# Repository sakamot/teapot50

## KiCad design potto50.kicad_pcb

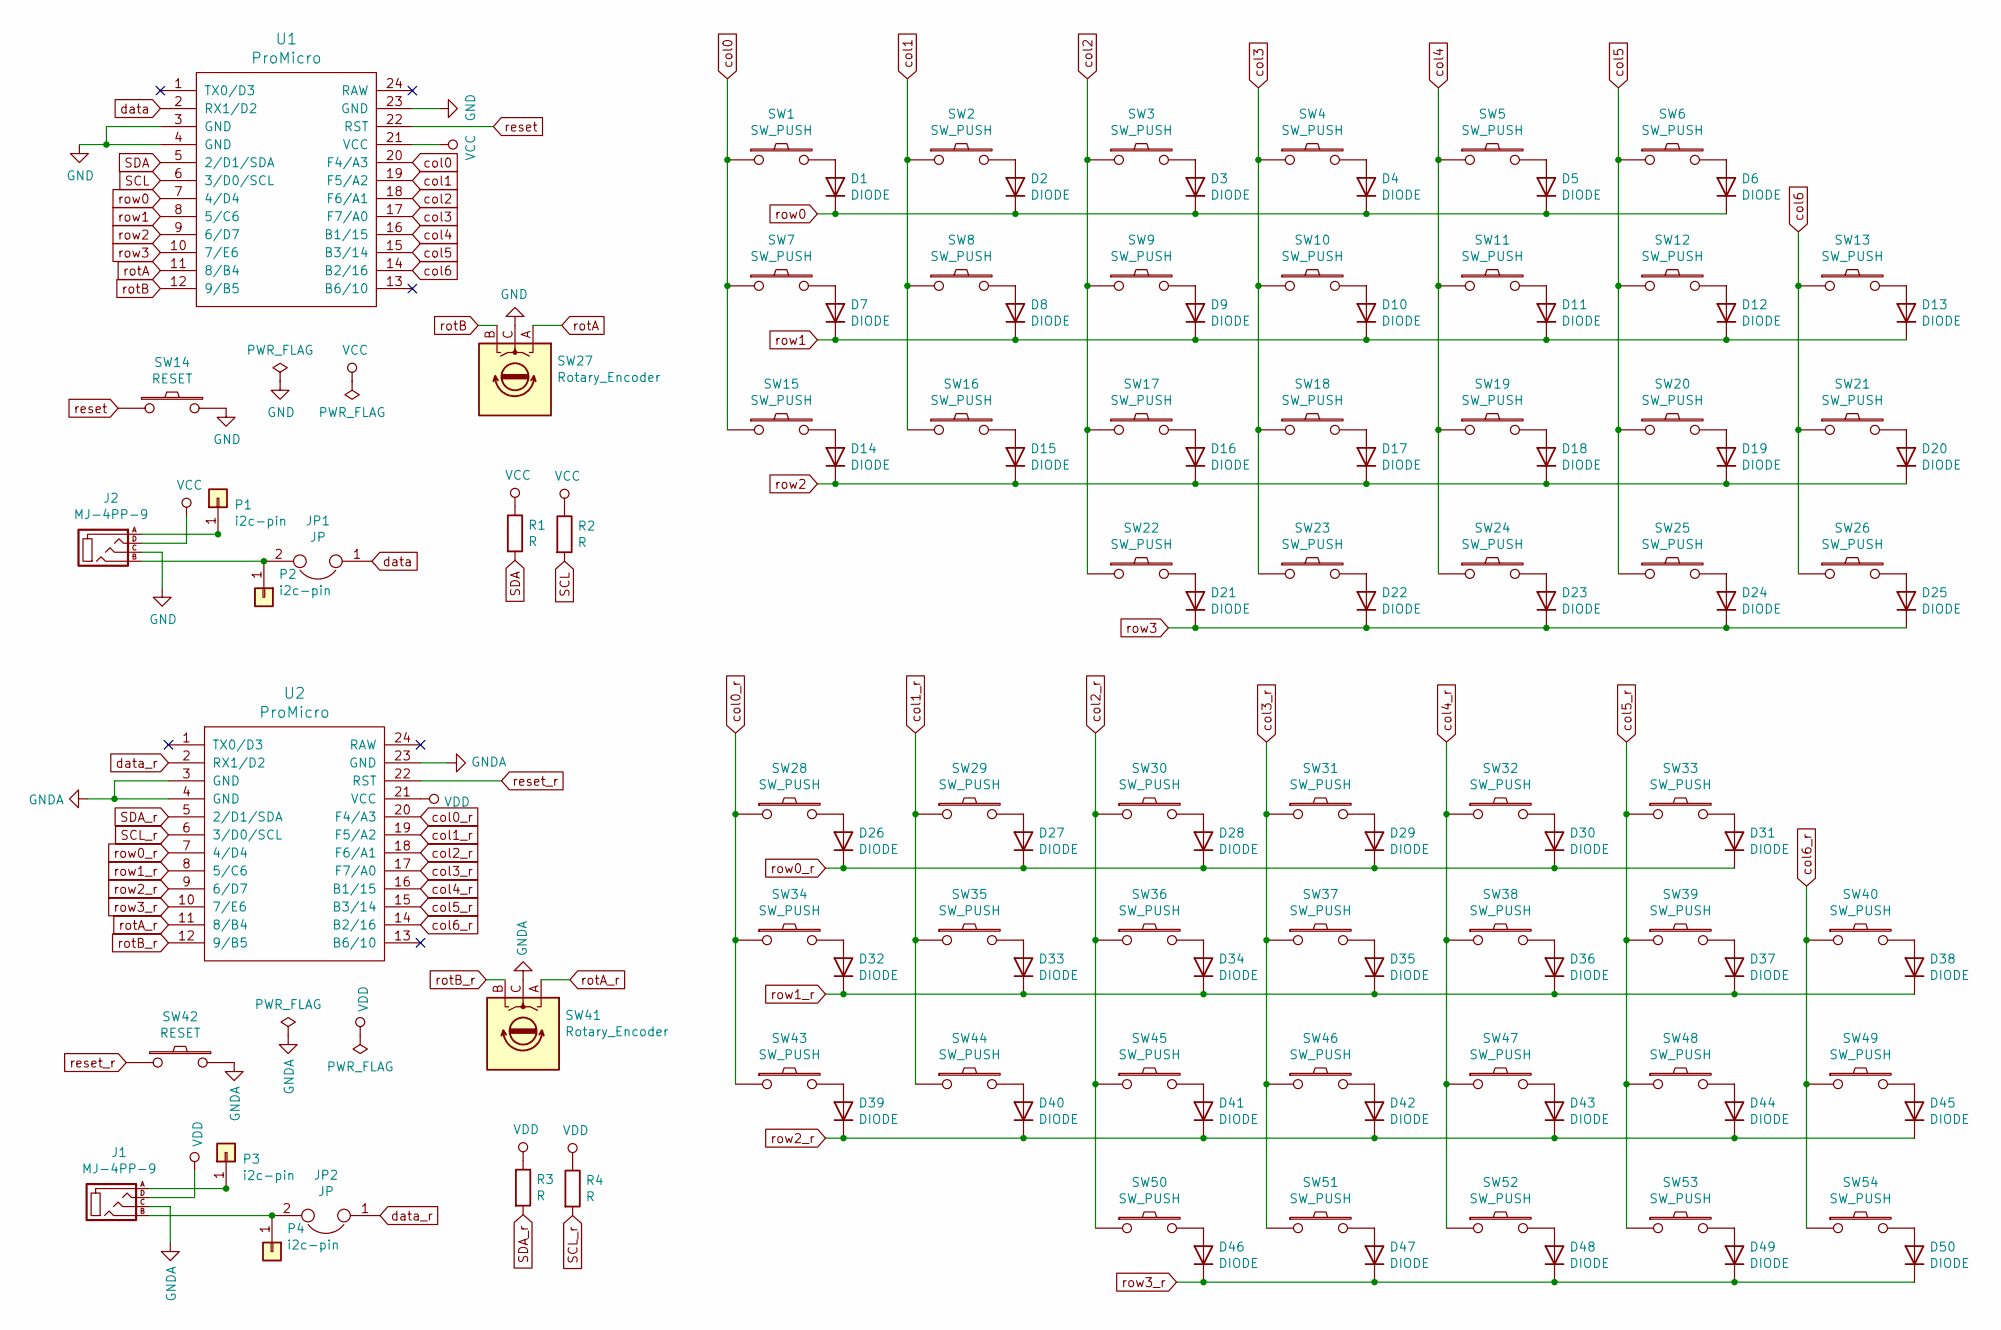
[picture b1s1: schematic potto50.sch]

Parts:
D1, D2, D3, D4, D5, D6, D7, D8, D9, D10, D11, D12, D13, D14, D15, D16, D17, D18, D19, D20, D21, D22, D23, D24, D25, D26, D27, D28, D29, D30, D31, D32, D33, D34, D35, D36, D37, D38, D39, D40, D41, D42, D43, D44, D45, D46, D47, D48, D49, D50: DIODE; D3_TH
J1, J2: MJ-4PP-9; MJ-4PP-9_1side
JP1, JP2: JP; Jumper
P1, P2, P3, P4: i2c-pin; 1pin_conn
R1, R2, R3, R4: R
SW1, SW2, SW3, SW4, SW5, SW6, SW7, SW8, SW9, SW10, SW11, SW12, SW13, SW15, SW16, SW17, SW18, SW19, SW20, SW21, SW22, SW23, SW24, SW25, SW26, SW28, SW29, SW30, SW31, SW32, SW33, SW34, SW35, SW36, SW37, SW38, SW39, SW40, SW43, SW44, SW45, SW46, SW47, SW48, SW49, SW50, SW51, SW52, SW53, SW54: SW_PUSH; CherryMX_1u
SW14, SW42: RESET; ResetSW
SW27, SW41: Rotary_Encoder; RotaryEncoder_Alps_EC12E_Vertical_H20mm
U1, U2: ProMicro; ProMicro_v2_1side

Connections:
GND: J2.C, SW14.2, SW27.C, U1.3 (GND), U1.4 (GND), U1.23 (GND)
GNDA: J1.C, SW41.C, SW42.2, U2.3 (GND), U2.4 (GND), U2.23 (GND)
unnamed: D1.1 (A), SW1.2
unnamed: D2.1 (A), SW2.2
unnamed: D3.1 (A), SW3.2
unnamed: D4.1 (A), SW4.2
unnamed: D5.1 (A), SW5.2
unnamed: D6.1 (A), SW6.2
unnamed: D7.1 (A), SW7.2
unnamed: D8.1 (A), SW8.2
unnamed: D9.1 (A), SW9.2
unnamed: D10.1 (A), SW10.2
unnamed: D11.1 (A), SW11.2
unnamed: D12.1 (A), SW12.2
unnamed: D13.1 (A), SW13.2
unnamed: D14.1 (A), SW15.2
unnamed: D15.1 (A), SW16.2
unnamed: D16.1 (A), SW17.2
unnamed: D17.1 (A), SW18.2
unnamed: D18.1 (A), SW19.2
unnamed: D19.1 (A), SW20.2
unnamed: D20.1 (A), SW21.2
unnamed: D21.1 (A), SW22.2
unnamed: D22.1 (A), SW23.2
unnamed: D23.1 (A), SW24.2
unnamed: D24.1 (A), SW25.2
unnamed: D25.1 (A), SW26.2
unnamed: D26.1 (A), SW28.2
unnamed: D27.1 (A), SW29.2
unnamed: D28.1 (A), SW30.2
unnamed: D29.1 (A), SW31.2
unnamed: D30.1 (A), SW32.2
unnamed: D31.1 (A), SW33.2
unnamed: D32.1 (A), SW34.2
unnamed: D33.1 (A), SW35.2
unnamed: D34.1 (A), SW36.2
unnamed: D35.1 (A), SW37.2
unnamed: D36.1 (A), SW38.2
unnamed: D37.1 (A), SW39.2
unnamed: D38.1 (A), SW40.2
unnamed: D39.1 (A), SW43.2
unnamed: D40.1 (A), SW44.2
unnamed: D41.1 (A), SW45.2
unnamed: D42.1 (A), SW46.2
unnamed: D43.1 (A), SW47.2
unnamed: D44.1 (A), SW48.2
unnamed: D45.1 (A), SW49.2
unnamed: D46.1 (A), SW50.2
unnamed: D47.1 (A), SW51.2
unnamed: D48.1 (A), SW52.2
unnamed: D49.1 (A), SW53.2
unnamed: D50.1 (A), SW54.2
unnamed: J1.A, P3.1
unnamed: J1.B, JP2.2, P4.1
unnamed: J2.A, P1.1
unnamed: J2.B, JP1.2, P2.1
SCL: R2.2, U1.6 (3/D0/SCL)
SCL_r: R4.2, U2.6 (3/D0/SCL)
SDA: R1.2, U1.5 (2/D1/SDA)
SDA_r: R3.2, U2.5 (2/D1/SDA)
VCC: J2.D, R1.1, R2.1, U1.21 (VCC)
VDD: J1.D, R3.1, R4.1, U2.21 (VCC)
col0: SW1.1, SW7.1, SW15.1, U1.20 (F4/A3)
col0_r: SW28.1, SW34.1, SW43.1, U2.20 (F4/A3)
col1: SW2.1, SW8.1, SW16.1, U1.19 (F5/A2)
col1_r: SW29.1, SW35.1, SW44.1, U2.19 (F5/A2)
col2: SW3.1, SW9.1, SW17.1, SW22.1, U1.18 (F6/A1)
col2_r: SW30.1, SW36.1, SW45.1, SW50.1, U2.18 (F6/A1)
col3: SW4.1, SW10.1, SW18.1, SW23.1, U1.17 (F7/A0)
col3_r: SW31.1, SW37.1, SW46.1, SW51.1, U2.17 (F7/A0)
col4: SW5.1, SW11.1, SW19.1, SW24.1, U1.16 (B1/15)
col4_r: SW32.1, SW38.1, SW47.1, SW52.1, U2.16 (B1/15)
col5: SW6.1, SW12.1, SW20.1, SW25.1, U1.15 (B3/14)
col5_r: SW33.1, SW39.1, SW48.1, SW53.1, U2.15 (B3/14)
col6: SW13.1, SW21.1, SW26.1, U1.14 (B2/16)
col6_r: SW40.1, SW49.1, SW54.1, U2.14 (B2/16)
data: JP1.1, U1.2 (RX1/D2)
data_r: JP2.1, U2.2 (RX1/D2)
reset: SW14.1, U1.22 (RST)
reset_r: SW42.1, U2.22 (RST)
rotA: SW27.A, U1.11 (8/B4)
rotA_r: SW41.A, U2.11 (8/B4)
rotB: SW27.B, U1.12 (9/B5)
rotB_r: SW41.B, U2.12 (9/B5)
row0: D1.2 (K), D2.2 (K), D3.2 (K), D4.2 (K), D5.2 (K), D6.2 (K), U1.7 (4/D4)
row0_r: D26.2 (K), D27.2 (K), D28.2 (K), D29.2 (K), D30.2 (K), D31.2 (K), U2.7 (4/D4)
row1: D7.2 (K), D8.2 (K), D9.2 (K), D10.2 (K), D11.2 (K), D12.2 (K), D13.2 (K), U1.8 (5/C6)
row1_r: D32.2 (K), D33.2 (K), D34.2 (K), D35.2 (K), D36.2 (K), D37.2 (K), D38.2 (K), U2.8 (5/C6)
row2: D14.2 (K), D15.2 (K), D16.2 (K), D17.2 (K), D18.2 (K), D19.2 (K), D20.2 (K), U1.9 (6/D7)
row2_r: D39.2 (K), D40.2 (K), D41.2 (K), D42.2 (K), D43.2 (K), D44.2 (K), D45.2 (K), U2.9 (6/D7)
row3: D21.2 (K), D22.2 (K), D23.2 (K), D24.2 (K), D25.2 (K), U1.10 (7/E6)
row3_r: D46.2 (K), D47.2 (K), D48.2 (K), D49.2 (K), D50.2 (K), U2.10 (7/E6)

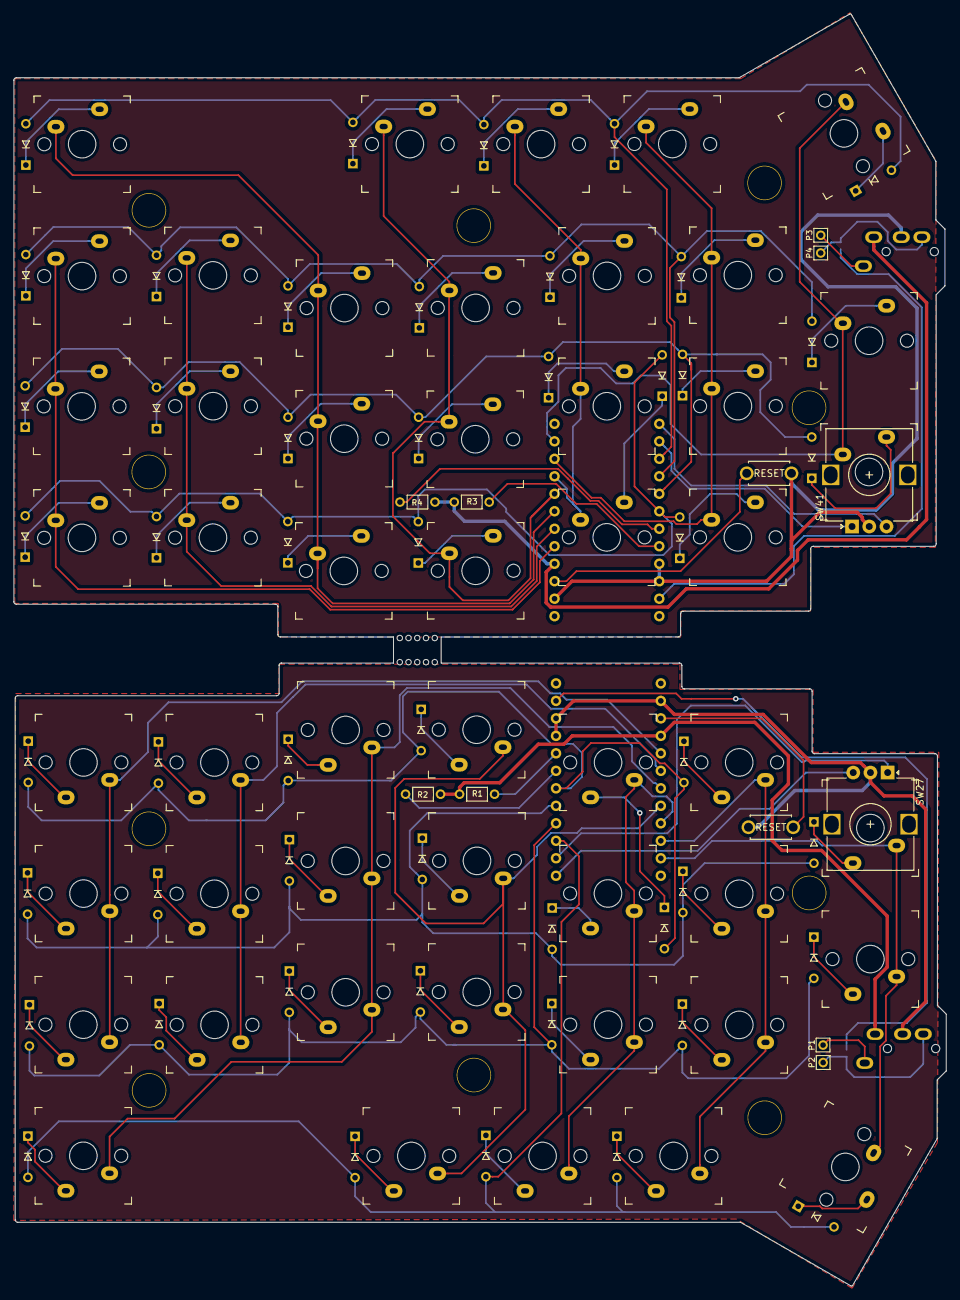
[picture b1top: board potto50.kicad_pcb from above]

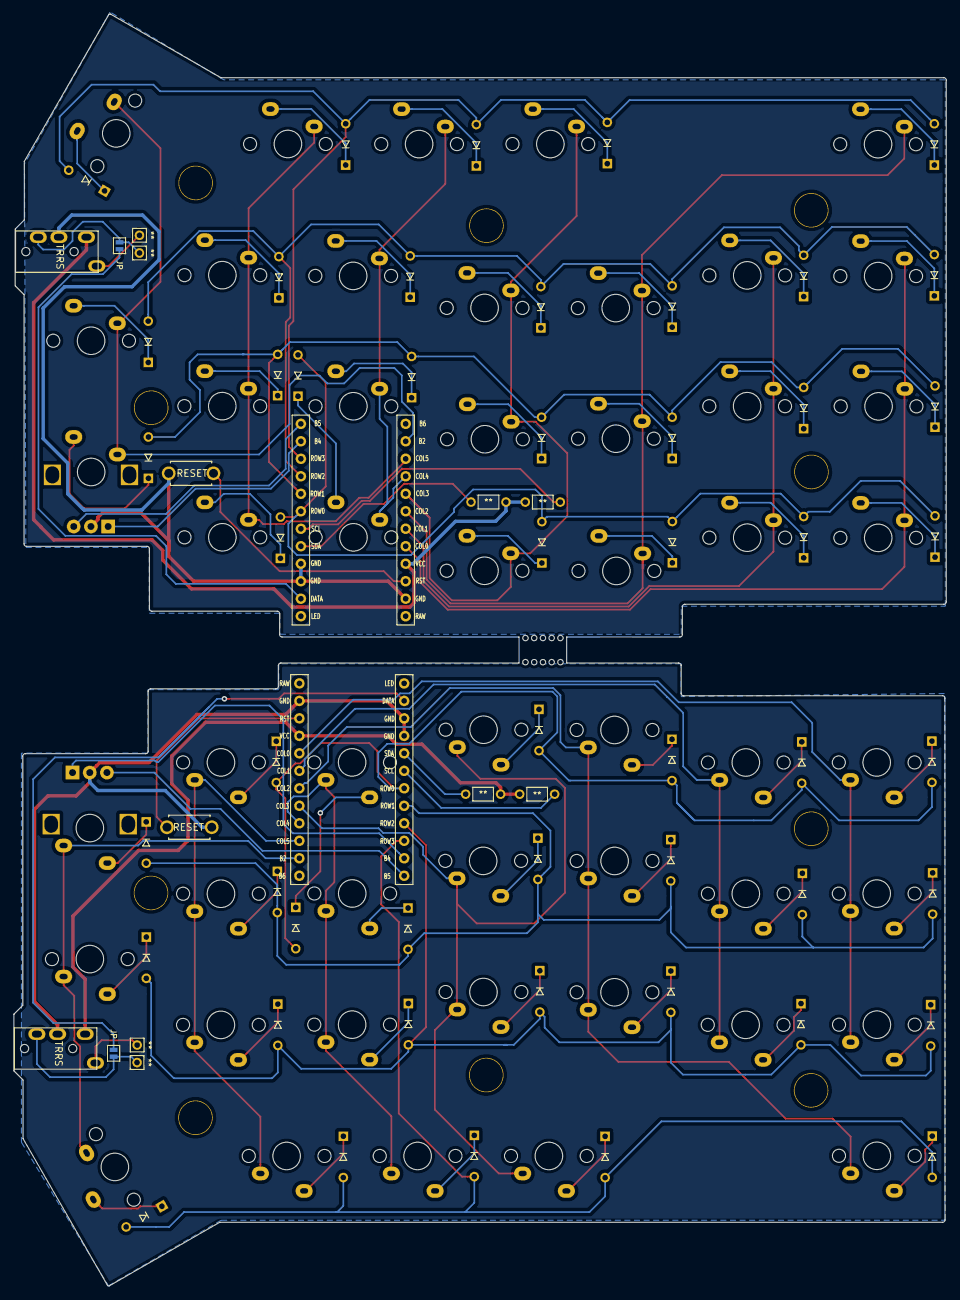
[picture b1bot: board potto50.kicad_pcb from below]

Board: 2 copper layers, 135.4 x 184.8 mm, 128 parts (11 on the bottom side), 92 nets.

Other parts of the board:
Ref**: Val**; HOLE
Ref**#2, Ref**#3, Ref**#4, Ref**#5, Ref**#6, Ref**#7, Ref**#8, Ref**#9, Ref**#10: Val**; HOLE
